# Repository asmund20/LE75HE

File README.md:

# XD75HE

XD75HE is a 60% Hall-effect keyboard PCB with 8kHz polling rate designed in the layout of the KPRepublic XD75RE.

## Features

- GH60 cases.
- Support for gummy O-ring mount cases **if the USB-C port is not soldered** e.g., Bakeneko60, and SingaKBD Unikorn (required 10mm JST cable).
- [libhmk](https://github.com/peppapighs/libhmk) firmware.
- [hmkconf](https://hmk.prasertsuk.com) web-based configurator.

## Disclaimer

- Work in progress. Do not attempt to fabricate yet.

You may change the Hall-effect sensors during the component selection based on your preference, and availability. Different sensors require different calibration values, which can be adjusted using the web-based configurator. Here are some options that I have used:

- GH39FKSW (Cheapest)
- MT9102ET
- SS39ET
- DRV5055A3
- OH49E-S (Discontinued)

The fabrication files above are available under releases.

## Case
Currently the only plate made is for the [kbdfansGT-60](https://kbdfans.com/collections/gt-60) case. Other gasket and top mount cases *might* use the same mounting, but I am not sure.

Plate fabrication files can be found in the folder named after the compatible case.

## Firmware
Firmware is not yet made, but will use libhmk.

Head to [libhmk](https://github.com/peppapighs/libhmk/releases) for a pre-compiled firmware. The firmware can be flashed using DFU mode, which can be entered by holding the BOOT button before plugging in. You may need to install the DFU bootloader driver using Zadig. See [libhmk](https://github.com/peppapighs/libhmk) for more information for firmware flashing instructions.

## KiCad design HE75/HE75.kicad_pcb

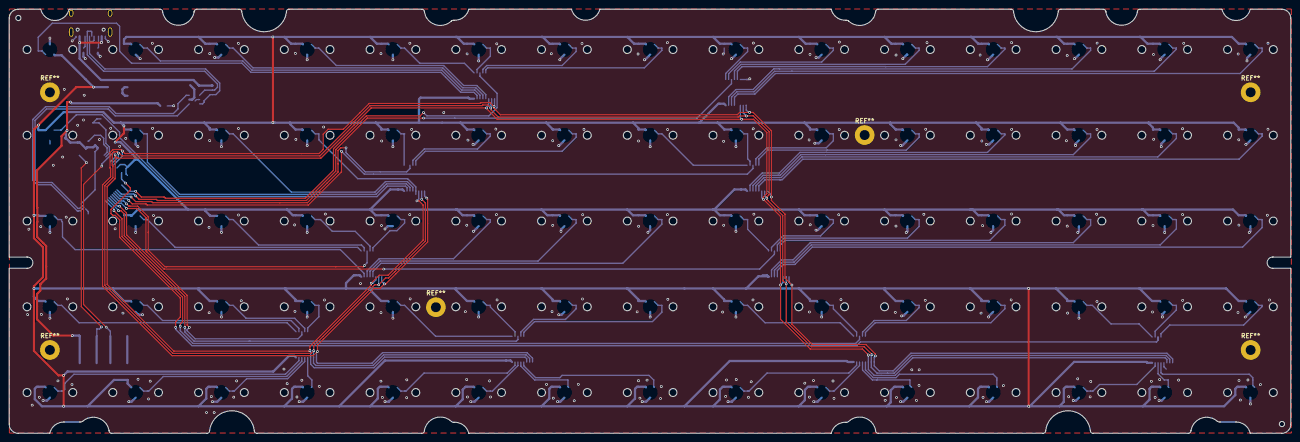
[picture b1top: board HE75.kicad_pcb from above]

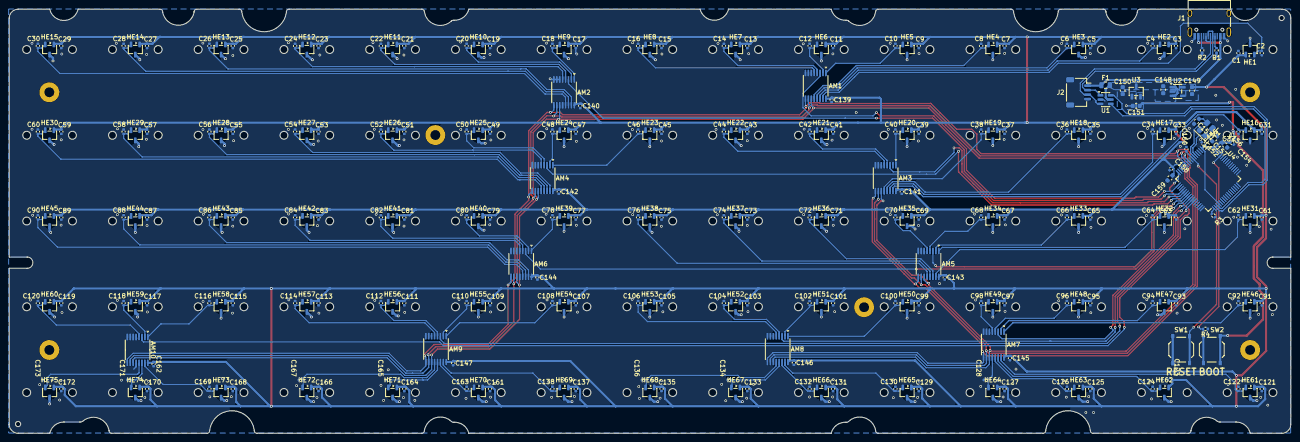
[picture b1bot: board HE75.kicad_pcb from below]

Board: 2 copper layers, 284.7 x 94.2 mm, 349 parts (272 on the bottom side), 104 nets.

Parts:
AM1, AM2, AM3, AM4, AM5, AM6, AM7, AM8, AM9, AM10: SN74LV4051A; TSSOP-16_4.4x5mm_P0.65mm
C1, C3, C5, C7, C9, C11, C13, C15, C17, C19, C21, C23, C25, C27, C29, C31, C33, C35, C37, C39, C41, C43, C45, C47, C49, C51, C53, C55, C57, C59, C61, C63, C65, C67, C69, C71, C73, C75, C77, C79, C81, C83, C85, C87, C89, C91, C93, C95, C97, C99, C101, C103, C105, C107, C109, C111, C113, C115, C117, C119, C121, C123, C125, C127, C129, C131, C133, C135, C137, C139, C140, C141, C142, C143, C144, C145, C146, C147, C154, C155, C156, C158, C160, C161, C162, C164, C166, C168, C170, C172: 100n; C_0402_1005Metric
C2, C4, C6, C8, C10, C12, C14, C16, C18, C20, C22, C24, C26, C28, C30, C32, C34, C36, C38, C40, C42, C44, C46, C48, C50, C52, C54, C56, C58, C60, C62, C64, C66, C68, C70, C72, C74, C76, C78, C80, C82, C84, C86, C88, C90, C92, C94, C96, C98, C100, C102, C104, C106, C108, C110, C112, C114, C116, C118, C120, C122, C124, C126, C128, C130, C132, C134, C136, C138, C163, C165, C167, C169, C171, C173: 4.7n; C_0402_1005Metric
C148, C149, C150, C151: 2.2u; C_0603_1608Metric
C152, C153: 30p; C_0603_1608Metric
C157: 10u; C_0603_1608Metric
C159: 1u; C_0603_1608Metric
F1: BSMD0805-050-24V; Fuse_0805_2012Metric
HE1, HE2, HE3, HE4, HE5, HE6, HE7, HE8, HE9, HE10, HE11, HE12, HE13, HE14, HE15, HE16, HE17, HE18, HE19, HE20, HE21, HE22, HE23, HE24, HE25, HE26, HE27, HE28, HE29, HE30, HE31, HE32, HE33, HE34, HE35, HE36, HE37, HE38, HE39, HE40, HE41, HE42, HE43, HE44, HE45, HE46, HE47, HE48, HE49, HE50, HE51, HE52, HE53, HE54, HE55, HE56, HE57, HE58, HE59, HE60, HE61, HE62, HE63, HE64, HE65, HE66, HE67, HE68, HE69, HE70, HE71, HE72, HE73, HE74, HE75: MT9102ET; SOT-23-3
J1: TYPE-C-31-M-12; USB_C_Receptacle_HRO_TYPE-C-31-M-12
J2: JST_SH; JST_SH_SM04B-SRSS-TB_1x04-1MP_P1.00mm_Horizontal
MX1, MX2, MX3, MX4, MX5, MX6, MX7, MX8, MX9, MX10, MX11, MX12, MX13, MX14, MX15, MX16, MX17, MX18, MX19, MX20, MX21, MX22, MX23, MX24, MX25, MX26, MX27, MX28, MX29, MX30, MX31, MX32, MX33, MX34, MX35, MX36, MX37, MX38, MX39, MX40, MX41, MX42, MX43, MX44, MX45, MX46, MX47, MX48, MX49, MX50, MX51, MX52, MX53, MX54, MX55, MX56, MX57, MX58, MX59, MX60, MX61, MX62, MX63, MX64, MX65, MX66, MX67, MX68, MX69, MX70, MX71, MX72, MX73, MX74, MX75: 1U; MX-1U
R1, R2: 5.1k; R_0402_1005Metric
R3, R4: 12k; R_0402_1005Metric
SW1, SW2: TS-1187A-B-A-B; SW_Push_1P1T_XKB_TS-1187A
TH1, TH2: ToolingHole
U1: USBLC6-2SC6; SOT-23-6
U2: TLV75733PDBV; SOT-23-5
U3: XC6206P332MR-G; SOT-23-3
U4: AT32F405RCT7; LQFP-64_10x10mm_P0.5mm
Y1: X322512MSB4SI; Crystal_SMD_3225-4Pin_3.2x2.5mm

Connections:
+3.3V: C151.1, C154.1, C155.1, C156.1, C157.1, SW2.2, U3.2 (VO), U4.1 (VDD), U4.36 (VDD), U4.64 (VDD)
+3.3VA: AM1.16 (VDD), AM2.16 (VDD), AM3.16 (VDD), AM4.16 (VDD), AM5.16 (VDD), AM6.16 (VDD), AM7.16 (VDD), AM8.16 (VDD), AM9.16 (VDD), AM10.16 (VDD), C1.1, C3.1, C5.1, C7.1, C9.1, C11.1, C13.1, C15.1, C17.1, C19.1, C21.1, C23.1, C25.1, C27.1, C29.1, C31.1, C33.1, C35.1, C37.1, C39.1, C41.1, C43.1, C45.1, C47.1, C49.1, C51.1, C53.1, C55.1, C57.1, C59.1, C61.1, C63.1, C65.1, C67.1, C69.1, C71.1, C73.1, C75.1, C77.1, C79.1, C81.1, C83.1, C85.1, C87.1, C89.1, C91.1, C93.1, C95.1, C97.1, C99.1, C101.1, C103.1, C105.1, C107.1, C109.1, C111.1, C113.1, C115.1, C117.1, C119.1, C121.1, C123.1, C125.1, C127.1, C129.1, C131.1, C133.1, C135.1, C137.1, C139.1, C140.1, C141.1, C142.1, C143.1, C144.1, C145.1, C146.1, C147.1, C149.1, C158.1, C159.1, C161.1, C162.1, C164.1, C166.1, C168.1, C170.1, C172.1, HE1.1 (VCC), HE2.1 (VCC), HE3.1 (VCC), HE4.1 (VCC), HE5.1 (VCC), HE6.1 (VCC), HE7.1 (VCC), HE8.1 (VCC), HE9.1 (VCC), HE10.1 (VCC), HE11.1 (VCC), HE12.1 (VCC), HE13.1 (VCC), HE14.1 (VCC), HE15.1 (VCC), HE16.1 (VCC), HE17.1 (VCC), HE18.1 (VCC), HE19.1 (VCC), HE20.1 (VCC), HE21.1 (VCC), HE22.1 (VCC), HE23.1 (VCC), HE24.1 (VCC), HE25.1 (VCC), HE26.1 (VCC), HE27.1 (VCC), HE28.1 (VCC), HE29.1 (VCC), HE30.1 (VCC), HE31.1 (VCC), HE32.1 (VCC), HE33.1 (VCC), HE34.1 (VCC), HE35.1 (VCC), HE36.1 (VCC), HE37.1 (VCC), HE38.1 (VCC), HE39.1 (VCC), HE40.1 (VCC), HE41.1 (VCC), HE42.1 (VCC), HE43.1 (VCC), HE44.1 (VCC), HE45.1 (VCC), HE46.1 (VCC), HE47.1 (VCC), HE48.1 (VCC), HE49.1 (VCC), HE50.1 (VCC), HE51.1 (VCC), HE52.1 (VCC), HE53.1 (VCC), HE54.1 (VCC), HE55.1 (VCC), HE56.1 (VCC), HE57.1 (VCC), HE58.1 (VCC), HE59.1 (VCC), HE60.1 (VCC), HE61.1 (VCC), HE62.1 (VCC), HE63.1 (VCC), HE64.1 (VCC), HE65.1 (VCC), HE66.1 (VCC), HE67.1 (VCC), HE68.1 (VCC), HE69.1 (VCC), HE70.1 (VCC), HE71.1 (VCC), HE72.1 (VCC), HE73.1 (VCC), HE74.1 (VCC), HE75.1 (VCC), U2.5 (OUT), U4.13 (VDDA)
+5V: C148.1, C150.1, F1.2, U1.5 (VBUS), U2.1 (IN), U2.3 (EN), U3.3 (VI)
BOOT0: R4.1, SW2.1, U4.60 (PF11/BOOT0)
GND: AM1.6 (Inh), AM1.7 (VEE), AM1.8 (VSS), AM2.6 (Inh), AM2.7 (VEE), AM2.8 (VSS), AM2.12 (X3), AM3.2 (X6), AM3.6 (Inh), AM3.7 (VEE), AM3.8 (VSS), AM4.6 (Inh), AM4.7 (VEE), AM4.8 (VSS), AM5.6 (Inh), AM5.7 (VEE), AM5.8 (VSS), AM6.6 (Inh), AM6.7 (VEE), AM6.8 (VSS), AM6.12 (X3), AM7.6 (Inh), AM7.7 (VEE), AM7.8 (VSS), AM8.6 (Inh), AM8.7 (VEE), AM8.8 (VSS), AM9.6 (Inh), AM9.7 (VEE), AM9.8 (VSS), AM10.5 (X5), AM10.6 (Inh), AM10.7 (VEE), AM10.8 (VSS), AM10.12 (X3), C1.2, C2.2, C3.2, C4.2, C5.2, C6.2, C7.2, C8.2, C9.2, C10.2, C11.2, C12.2, C13.2, C14.2, C15.2, C16.2, C17.2, C18.2, C19.2, C20.2, C21.2, C22.2, C23.2, C24.2, C25.2, C26.2, C27.2, C28.2, C29.2, C30.2, C31.2, C32.2, C33.2, C34.2, C35.2, C36.2, C37.2, C38.2, C39.2, C40.2, C41.2, C42.2, C43.2, C44.2, C45.2, C46.2, C47.2, C48.2, C49.2, C50.2, C51.2, C52.2, C53.2, C54.2, C55.2, C56.2, C57.2, C58.2, C59.2, C60.2, C61.2, C62.2, C63.2, C64.2, C65.2, C66.2, C67.2, C68.2, C69.2, C70.2, C71.2, C72.2, C73.2, C74.2, C75.2, C76.2, C77.2, C78.2, C79.2, C80.2, C81.2, C82.2, C83.2, C84.2, C85.2, C86.2, C87.2, C88.2, C89.2, C90.2, C91.2, C92.2, C93.2, C94.2, C95.2, C96.2, C97.2, C98.2, C99.2, C100.2, C101.2, C102.2, C103.2, C104.2, C105.2, C106.2, C107.2, C108.2, C109.2, C110.2, C111.2, C112.2, C113.2, C114.2, C115.2, C116.2, C117.2, C118.2, C119.2, C120.2, C121.2, C122.2, C123.2, C124.2, C125.2, C126.2, C127.2, C128.2, C129.2, C130.2, C131.2, C132.2, C133.2, C134.2, C135.2, C136.2, C137.2, C138.2, C139.2, C140.2, C141.2, C142.2, C143.2, C144.2, C145.2, C146.2, C147.2, C148.2, C149.2, C150.2, C151.2, C152.2, C153.2, C154.2, C155.2, C156.2, C157.2, C158.2, C159.2, C160.2, C161.2, C162.2, C163.2, C164.2, C165.2, C166.2, C167.2, C168.2, C169.2, C170.2, C171.2, C172.2, C173.2, HE1.3 (GND), HE2.3 (GND), HE3.3 (GND), HE4.3 (GND), HE5.3 (GND), HE6.3 (GND), HE7.3 (GND), HE8.3 (GND), HE9.3 (GND), HE10.3 (GND), HE11.3 (GND), HE12.3 (GND), HE13.3 (GND), HE14.3 (GND), HE15.3 (GND), HE16.3 (GND), HE17.3 (GND), HE18.3 (GND), HE19.3 (GND), HE20.3 (GND), HE21.3 (GND), HE22.3 (GND), HE23.3 (GND), HE24.3 (GND), HE25.3 (GND), HE26.3 (GND), HE27.3 (GND), HE28.3 (GND), HE29.3 (GND), HE30.3 (GND), HE31.3 (GND), HE32.3 (GND), HE33.3 (GND), HE34.3 (GND), HE35.3 (GND), HE36.3 (GND), HE37.3 (GND), HE38.3 (GND), HE39.3 (GND), HE40.3 (GND), HE41.3 (GND), HE42.3 (GND), HE43.3 (GND), HE44.3 (GND), HE45.3 (GND), HE46.3 (GND), HE47.3 (GND), HE48.3 (GND), HE49.3 (GND), HE50.3 (GND), HE51.3 (GND), HE52.3 (GND), HE53.3 (GND), HE54.3 (GND), HE55.3 (GND), HE56.3 (GND), HE57.3 (GND), HE58.3 (GND), HE59.3 (GND), HE60.3 (GND), HE61.3 (GND), HE62.3 (GND), HE63.3 (GND), HE64.3 (GND), HE65.3 (GND), HE66.3 (GND), HE67.3 (GND), HE68.3 (GND), HE69.3 (GND), HE70.3 (GND), HE71.3 (GND), HE72.3 (GND), HE73.3 (GND), HE74.3 (GND), HE75.3 (GND), J1.A1 (GND), J1.A12 (GND), J1.B1 (GND), J1.B12 (GND), J1.S1 (SHIELD), J2.4, R1.2, R2.1, R3.1, R4.2, SW1.2, U1.2 (GND), U2.2 (GND), U3.1 (GND), U4.12 (VSSA), U4.31 (VSS), U4.63 (VSS), Y1.2, Y1.4
HE1: AM1.15 (X2), C2.1, HE1.2 (OUT)
HE2: AM1.14 (X1), C4.1, HE2.2 (OUT)
HE3: AM1.13 (X0), C6.1, HE3.2 (OUT)
HE4: AM1.12 (X3), C8.1, HE4.2 (OUT)
HE5: AM1.1 (X4), C10.1, HE5.2 (OUT)
HE6: AM1.2 (X6), C12.1, HE6.2 (OUT)
HE7: AM1.4 (X7), C14.1, HE7.2 (OUT)
HE8: AM1.5 (X5), C16.1, HE8.2 (OUT)
HE9: AM2.1 (X4), C18.1, HE9.2 (OUT)
HE10: AM2.2 (X6), C20.1, HE10.2 (OUT)
HE11: AM2.4 (X7), C22.1, HE11.2 (OUT)
HE12: AM2.5 (X5), C24.1, HE12.2 (OUT)
HE13: AM2.15 (X2), C26.1, HE13.2 (OUT)
HE14: AM2.14 (X1), C28.1, HE14.2 (OUT)
HE15: AM2.13 (X0), C30.1, HE15.2 (OUT)
HE16: AM3.15 (X2), C32.1, HE16.2 (OUT)
HE17: AM3.14 (X1), C34.1, HE17.2 (OUT)
HE18: AM3.13 (X0), C36.1, HE18.2 (OUT)
HE19: AM3.12 (X3), C38.1, HE19.2 (OUT)
HE20: AM3.1 (X4), C40.1, HE20.2 (OUT)
HE21: AM3.4 (X7), C42.1, HE21.2 (OUT)
HE22: AM3.5 (X5), C44.1, HE22.2 (OUT)
HE23: AM4.1 (X4), C46.1, HE23.2 (OUT)
HE24: AM4.2 (X6), C48.1, HE24.2 (OUT)
HE25: AM4.4 (X7), C50.1, HE25.2 (OUT)
HE26: AM4.5 (X5), C52.1, HE26.2 (OUT)
HE27: AM4.15 (X2), C54.1, HE27.2 (OUT)
HE28: AM4.14 (X1), C56.1, HE28.2 (OUT)
HE29: AM4.13 (X0), C58.1, HE29.2 (OUT)
HE30: AM4.12 (X3), C60.1, HE30.2 (OUT)
HE31: AM5.15 (X2), C62.1, HE31.2 (OUT)
HE32: AM5.1 (X4), C64.1, HE32.2 (OUT)
HE33: AM5.2 (X6), C66.1, HE33.2 (OUT)
HE34: AM5.4 (X7), C68.1, HE34.2 (OUT)
HE35: AM5.5 (X5), C70.1, HE35.2 (OUT)
HE36: AM5.14 (X1), C72.1, HE36.2 (OUT)
HE37: AM5.13 (X0), C74.1, HE37.2 (OUT)
HE38: AM5.12 (X3), C76.1, HE38.2 (OUT)
HE39: AM6.1 (X4), C78.1, HE39.2 (OUT)
HE40: AM6.2 (X6), C80.1, HE40.2 (OUT)
HE41: AM6.4 (X7), C82.1, HE41.2 (OUT)
HE42: AM6.5 (X5), C84.1, HE42.2 (OUT)
HE43: AM6.15 (X2), C86.1, HE43.2 (OUT)
HE44: AM6.14 (X1), C88.1, HE44.2 (OUT)
HE45: AM6.13 (X0), C90.1, HE45.2 (OUT)
HE46: AM7.1 (X4), C92.1, HE46.2 (OUT)
HE47: AM7.2 (X6), C94.1, HE47.2 (OUT)
HE48: AM7.4 (X7), C96.1, HE48.2 (OUT)
HE49: AM7.5 (X5), C98.1, HE49.2 (OUT)
HE50: AM8.1 (X4), C100.1, HE50.2 (OUT)
HE51: AM8.2 (X6), C102.1, HE51.2 (OUT)
HE52: AM8.4 (X7), C104.1, HE52.2 (OUT)
HE53: AM8.5 (X5), C106.1, HE53.2 (OUT)
HE54: AM9.1 (X4), C108.1, HE54.2 (OUT)
HE55: AM9.2 (X6), C110.1, HE55.2 (OUT)
HE56: AM9.4 (X7), C112.1, HE56.2 (OUT)
HE57: AM9.5 (X5), C114.1, HE57.2 (OUT)
HE58: AM10.1 (X4), C116.1, HE58.2 (OUT)
HE59: AM10.2 (X6), C118.1, HE59.2 (OUT)
HE60: AM10.4 (X7), C120.1, HE60.2 (OUT)
HE61: AM7.15 (X2), C122.1, HE61.2 (OUT)
HE62: AM7.14 (X1), C124.1, HE62.2 (OUT)
HE63: AM7.13 (X0), C126.1, HE63.2 (OUT)
HE64: AM7.12 (X3), C128.1, HE64.2 (OUT)
HE65: AM8.15 (X2), C130.1, HE65.2 (OUT)
HE66: AM8.14 (X1), C132.1, HE66.2 (OUT)
HE67: AM8.13 (X0), C134.1, HE67.2 (OUT)
HE68: AM8.12 (X3), C136.1, HE68.2 (OUT)
HE69: AM9.15 (X2), C138.1, HE69.2 (OUT)
HE70: AM9.14 (X1), C163.1, HE70.2 (OUT)
HE71: AM9.13 (X0), C165.1, HE71.2 (OUT)
HE72: AM9.12 (X3), C167.1, HE72.2 (OUT)
HE73: AM10.15 (X2), C169.1, HE73.2 (OUT)
HE74: AM10.14 (X1), C171.1, HE74.2 (OUT)
HE75: AM10.13 (X0), C173.1, HE75.2 (OUT)
HEXT_IN: C152.1, U4.5 (PF0/HEXT_IN), Y1.1
HEXT_OUT: C153.1, U4.6 (PF1/HEXT_OUT), Y1.3
MUX_OUT_1: AM1.3 (X), U4.17 (PA3)
MUX_OUT_2: AM2.3 (X), U4.20 (PA4)
MUX_OUT_3: AM3.3 (X), U4.21 (PA5)
MUX_OUT_4: AM4.3 (X), U4.22 (PA6)
MUX_OUT_5: AM5.3 (X), U4.23 (PA7)
MUX_OUT_6: AM6.3 (X), U4.24 (PC4)
MUX_OUT_7: AM7.3 (X), U4.25 (PC5)
MUX_OUT_8: AM8.3 (X), U4.26 (PB0)
MUX_OUT_9: AM9.3 (X), U4.27 (PB1)
MUX_OUT_10: AM10.3 (X), U4.16 (PA2)
MUX_SELECT_0: AM1.11 (A), AM2.11 (A), AM3.11 (A), AM4.11 (A), AM5.11 (A), AM6.11 (A), AM7.11 (A), AM8.11 (A), AM9.11 (A), AM10.11 (A), U4.9 (PC1)
MUX_SELECT_1: AM1.10 (B), AM2.10 (B), AM3.10 (B), AM4.10 (B), AM5.10 (B), AM6.10 (B), AM7.10 (B), AM8.10 (B), AM9.10 (B), AM10.10 (B), U4.10 (PC2)
MUX_SELECT_2: AM1.9 (C), AM2.9 (C), AM3.9 (C), AM4.9 (C), AM5.9 (C), AM6.9 (C), AM7.9 (C), AM8.9 (C), AM9.9 (C), AM10.9 (C), U4.11 (PC3)
NRST: C160.1, SW1.1, U4.7 (NRST)
unnamed: J1.A5 (CC1), R1.1
unnamed: J1.B5 (CC2), R2.2
unnamed: R3.2, U4.33 (OTGHS1_R)
USB_D+: U1.4 (I/O2), U4.35 (OTGHS1_D+)
USB_D-: U1.6 (I/O1), U4.34 (OTGHS1_D-)
USB_PLUG_D+: J1.A6 (D+), J1.B6 (D+), J2.3, U1.3 (I/O2)
USB_PLUG_D-: J1.A7 (D-), J1.B7 (D-), J2.2, U1.1 (I/O1)
VBUS: F1.1, J1.A4 (VBUS), J1.A9 (VBUS), J1.B4 (VBUS), J1.B9 (VBUS), J2.1
